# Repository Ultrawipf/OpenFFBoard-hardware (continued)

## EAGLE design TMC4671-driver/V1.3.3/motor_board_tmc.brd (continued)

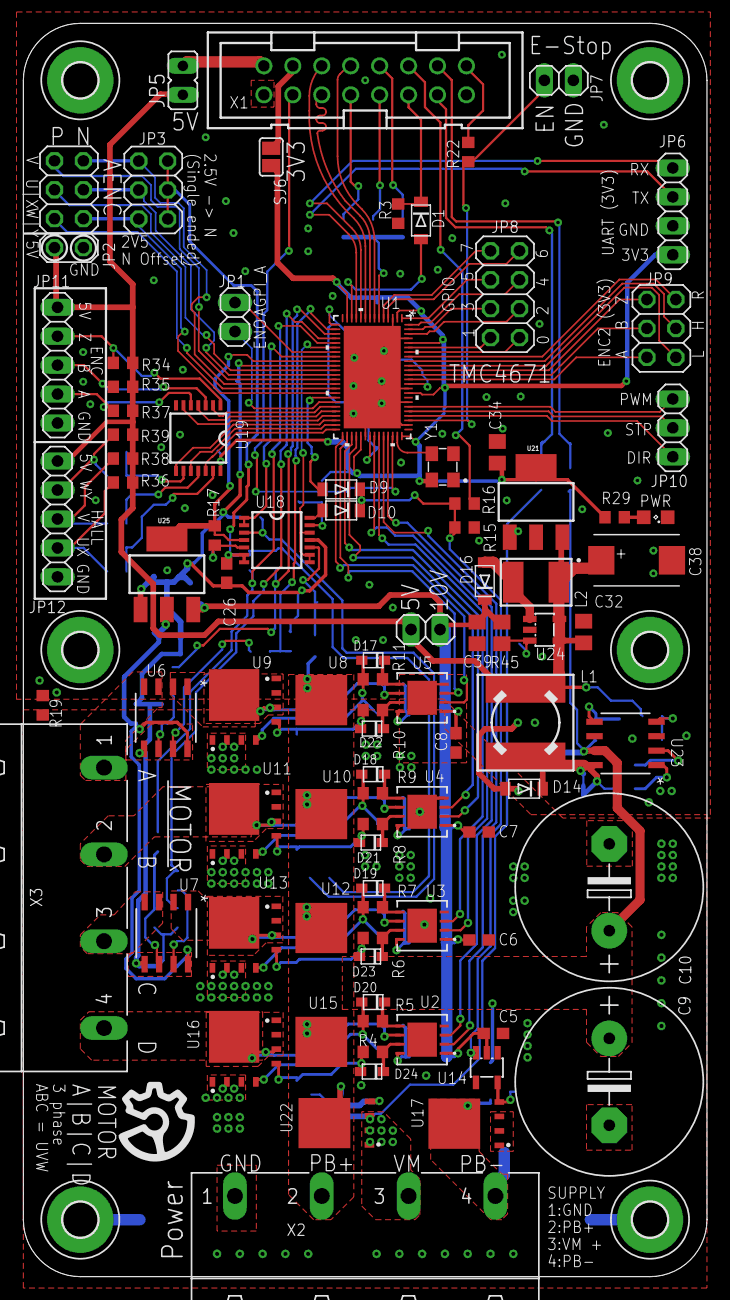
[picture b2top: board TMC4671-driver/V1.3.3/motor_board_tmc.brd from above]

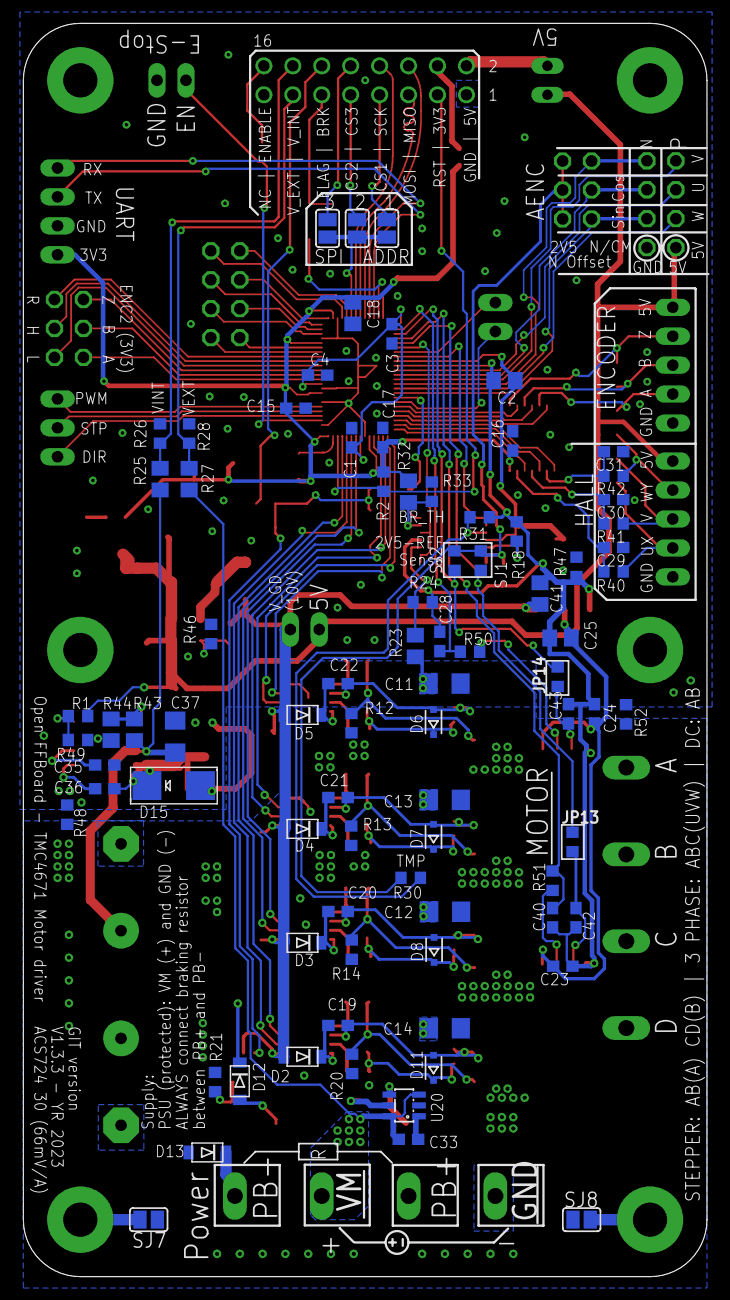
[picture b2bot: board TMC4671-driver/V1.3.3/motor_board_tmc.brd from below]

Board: 2 copper layers, 60.0 x 110.0 mm, 178 parts (82 on the bottom side), 136 nets.

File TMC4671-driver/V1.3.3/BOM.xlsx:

Comment | Designator | Footprint | Notes
3.3V Ldo 1117 | U21 | SOT223
1.5k | R16, R22, R24, R29, R31, R40, R41, R42 | R0603
100nF | C1, C3, C4, C5, C6, C7, C8, C15, C16, C17, C19, C20, C21, C22, C23, C24, C26, C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 | C0603
10k | R2, R3, R15, R17, R18, R26, R28, R46 | R0603
ERTJ1VR103J | R30 | R0603 | digikey https://www.digikey.de/en/products/detail/panasonic-electron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
10µH LQH43PN100M26L | L2 | L4532P | digikey
4.7nF | C42, C43,C29, C30, C31 | C0603 |  |  | Depends on sensor variant
1µF | C11, C12, C13, C14, C37 | C1206
15 | R4, R5, R6, R7, R8, R9, R10, R11 | R0603
220µH 74404084221 | L1 | 8MM INDUCTOR | digikey
25MHz | Y1 | ECS-327KE-TR
294k | R25, R27, R43 | R0805
33k | R12, R13, R14, R20, R21 | R0603
4.7k | R34, R35, R36, R37, R38, R39 | R0603
10µF | C2, C18, C25, C32, C34, C39, C41 | C0805
47k | R33 | R0603 |  |  | Brake resistor emergency point
593D476X0016D2TE3 | C38 | CAPPM7343X310N
680µF EEU-FS1K681B | C9, C10 | E7,5-16 | https://www.digikey.de/en/products/detail/panasonic-electron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 |  | https://www.arrow.com/en/products/eeu-fs1k681b/panasonic?q=E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
71.5k | R23, R32, R44, R45 | R0805
74LV17APWJ | U19 | TSSOP14 | digikey
AP3012KTR-G1 | U24 | SOT23-5L
NTMFSC2D9N08H | U8, U9, U10, U11, U12, U13, U15, U16, U17,U22 | POWERTFDN8 | Or FDMS86181, BSC030N08NS5 (20ohm gates minimum)
BZX384-XXX | D6, D7, D8, D11 | SOD323-R
Green | LED1 | SML0805
HV >100V | D2, D3, D4, D5, D12, D14 | SOD-123FL | Must handle 500mA+
LM5109BSD | U2, U3, U4, U5 | SDC08A
LM74700-Q1 | U20 | SOT23-6 | https://www.digikey.de/en/products/detail/texas-instruments/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
LV low drop diode (<10V) | D1, D9, D10, D16 | SOD-123FL | Fast gate discharge
max5035dasa | U23 | 8-SOIC
MCP1402T-E | U14 | SOT23-5L
MCP6004 | U18 | TSSOP14
TMC4671 | U1 | QFN76_10P5X6P5
5V LDO 1117 | U25 | SOT223
STPS30120DJF-TR | (U22) | PowerFLAT-5x6 | If no LM74700 is used. Otherwise use another mosfet here
SMA HV diode | D15 | SMA Diode | For DC converter
ACS724 | U6,U7
0 | R50,R51,R47, R48 | R0603 | For ACS724
0 | sj1,sj2,SJ3 | R0805 | For ACS724
47k | R1 | R0603 | 5v FB for max5035D
15k | R49 | R0603

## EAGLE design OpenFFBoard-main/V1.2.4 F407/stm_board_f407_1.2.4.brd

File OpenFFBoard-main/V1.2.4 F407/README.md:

### FFBoard main USB interface F407VG
This is the heart of the Open FFBoard.
It runs the FFBoard firmware and interfaces with all your peripherals and motor drivers.

V1.2.3 and 1.2.4 is a USB-C version and adds additional USB protections.
The SPI1 port layout had to change to 2 rows instead of 1.

#### How to order yourself
You can order this board directly via [jlcpcb.com](https://jlcpcb.com/?from=Gigawipf).

The BOM and component placement files are available in the JLC assembly folder and already formatted with matching LCSC part numbers.

Everything apart from the headers can be directly assembled by JLC including the USB socket.

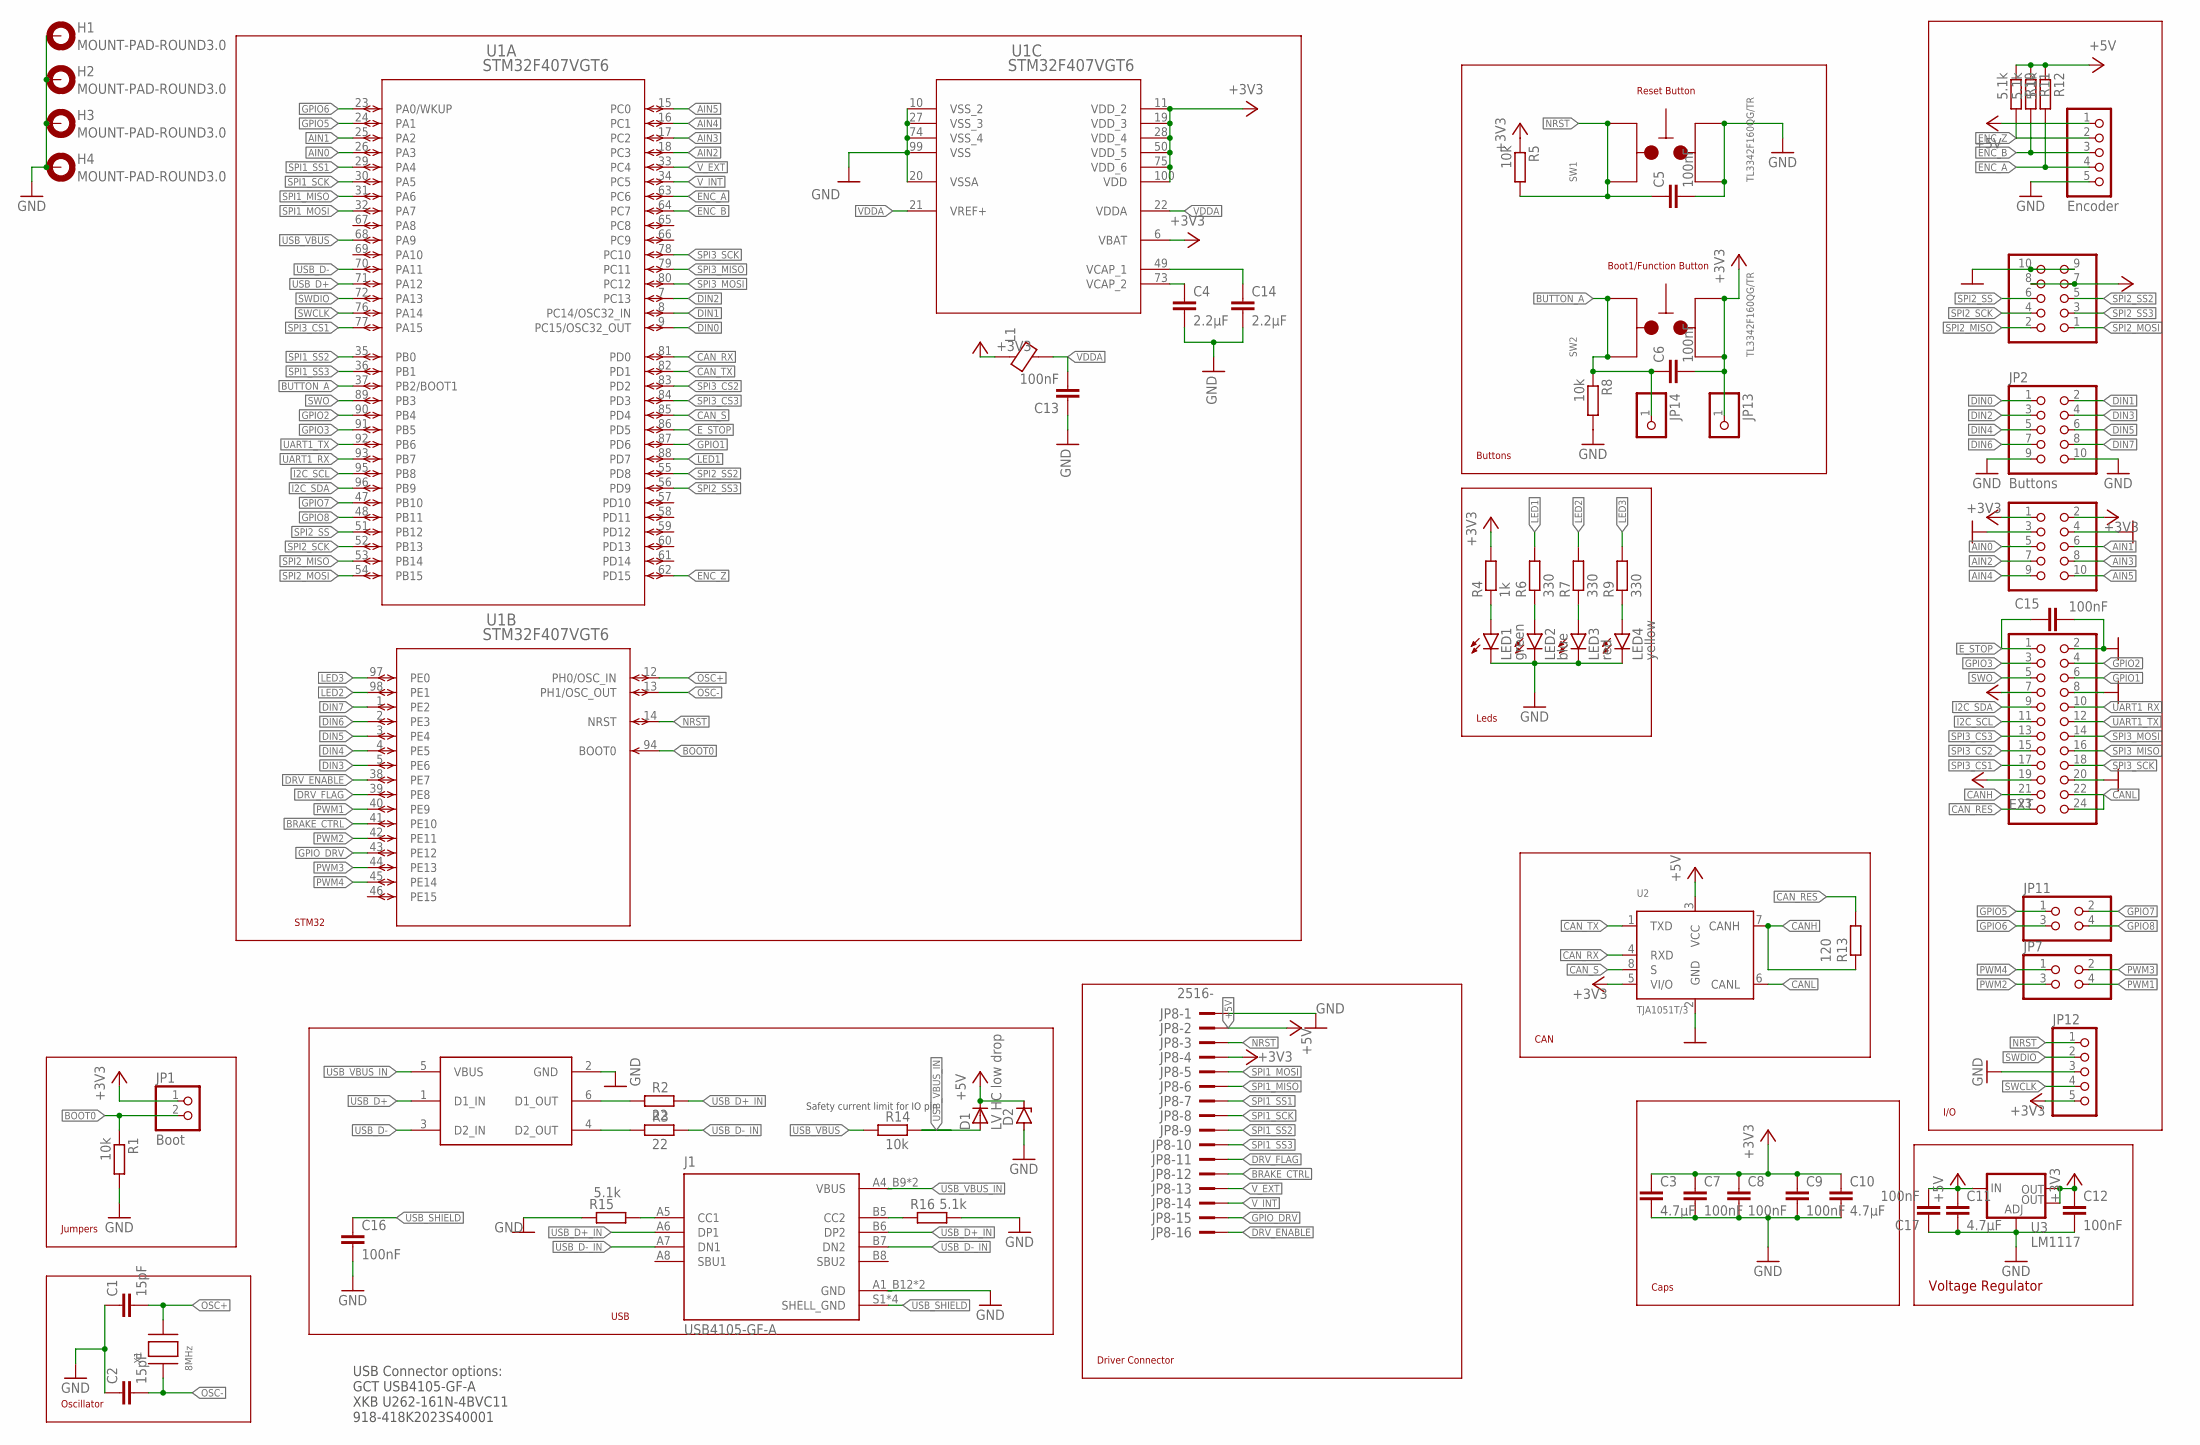
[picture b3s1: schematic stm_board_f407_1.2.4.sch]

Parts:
C1, C2: 15pF; C0603
C3, C10, C11: 4.7µF; C0805
C4, C14: 2.2µF; C0603
C5, C6, C7, C8, C9, C12, C13, C15, C16, C17: 100nF; C0603
D1: LV HC low drop; SMADIODE
D2: ZENER-DIODESOD80C; SOD80C
H1, H2, H3, H4: MOUNT-PAD-ROUND3.0; 3,0-PAD
J1: USB4105-GF-A; GCT_USB4105-GF-A
JP1: Boot; 1X02
JP2: Buttons; 2X05
JP3: Analog; 2X05
JP4: EXT; 2X12
JP5: Encoder; 1X05
JP6: SPI; 2X05
JP7, JP11: PINHD-2X2; 2X02
JP8: 2516-; PAK100/2500-16
JP12: PINHD-1X5; 1X05
JP13, JP14: PINHD-1X1; 1X01
L1: GZ2012D601TF; BLM21PG331SN1D
LED1: green; SML0805
LED2: blue; SML0805
LED3: red; SML0805
LED4: yellow; SML0805
R1, R5, R8, R14: 10k; R0603
R2, R3: 22; R0603
R4: 1k; R0603
R6, R7, R9: 330; R0603
R10, R11, R12, R15, R16: 5.1k; R0603
R13: 120; R0603
SW1, SW2: TL3342F160QG/TR
U1: STM32F407VGT6; LQFP100-14X14MM
U2: TJA1051T/3; SOT96-1
U3: LM1117; SOT223
U4: USBLC6-2SC6; TSOT-23-6
X1: 8MHz; NX5032

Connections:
+3V3: C3.1, C6.2, C7.1, C8.1, C9.1, C10.1, C12.1, JP1.1, JP3.1, JP3.2, JP4.7, JP6.7, JP6.8, JP8.4, JP12.5, JP13.1, L1.1, R4.2, R5.1, SW2.1, SW2.2, U1.6 (VBAT), U1.11 (VDD_2), U1.19 (VDD_3), U1.28 (VDD_4), U1.50 (VDD_5), U1.75 (VDD_6), U1.100 (VDD), U2.5 (VI/O), U3.2 (OUT), U3.4 (OUT)
+5V: C11.1, C17.2, D1.C, D2.C, JP4.19, JP5.1, JP8.2, R10.1, R11.1, R12.1, U2.3 (VCC), U3.3 (IN)
AIN0: JP3.5, U1.26 (PA3)
AIN1: JP3.6, U1.25 (PA2)
AIN2: JP3.7, U1.18 (PC3)
AIN3: JP3.8, U1.17 (PC2)
AIN4: JP3.9, U1.16 (PC1)
AIN5: JP3.10, U1.15 (PC0)
BOOT0: JP1.2, R1.1, U1.94 (BOOT0)
BRAKE_CTRL: JP8.12, U1.41 (PE10)
BUTTON_A: C6.1, JP14.1, R8.1, SW2.3, SW2.4, U1.37 (PB2/BOOT1)
CANH: JP4.21, R13.1, U2.7 (CANH)
CANL: JP4.22, JP4.24, U2.6 (CANL)
CAN_RES: JP4.23, R13.2
CAN_RX: U1.81 (PD0), U2.4 (RXD)
CAN_S: U1.85 (PD4), U2.8 (S)
CAN_TX: U1.82 (PD1), U2.1 (TXD)
DIN0: JP2.1, U1.9 (PC15/OSC32_OUT)
DIN1: JP2.2, U1.8 (PC14/OSC32_IN)
DIN2: JP2.3, U1.7 (PC13)
DIN3: JP2.4, U1.5 (PE6)
DIN4: JP2.5, U1.4 (PE5)
DIN5: JP2.6, U1.3 (PE4)
DIN6: JP2.7, U1.2 (PE3)
DIN7: JP2.8, U1.1 (PE2)
DRV_ENABLE: JP8.16, U1.38 (PE7)
DRV_FLAG: JP8.11, U1.39 (PE8)
ENC_A: JP5.4, R12.2, U1.63 (PC6)
ENC_B: JP5.3, R11.2, U1.64 (PC7)
ENC_Z: JP5.2, R10.2, U1.62 (PD15)
E_STOP: C15.1, JP4.1, U1.86 (PD5)
GND: C1.1, C2.1, C3.2, C4.2, C5.2, C7.2, C8.2, C9.2, C10.2, C11.2, C12.2, C13.1, C14.2, C15.2, C16.2, C17.1, D2.A, H1.B3,0, H2.B3,0, H3.B3,0, H4.B3,0, J1.A1_B12 (GND), J1.B1_A12 (GND), JP2.9, JP2.10, JP3.3, JP3.4, JP4.2, JP4.8, JP4.20, JP5.5, JP6.9, JP6.10, JP8.1, JP12.3, LED1.C, LED2.C, LED3.C, LED4.C, R1.2, R8.2, R15.1, R16.2, SW1.1, SW1.2, U1.10 (VSS_2), U1.20 (VSSA), U1.27 (VSS_3), U1.74 (VSS_4), U1.99 (VSS), U2.2 (GND), U3.1 (ADJ), U4.2 (GND)
GPIO1: JP4.6, U1.87 (PD6)
GPIO2: JP4.4, U1.90 (PB4)
GPIO3: JP4.3, U1.91 (PB5)
GPIO5: JP11.1, U1.24 (PA1)
GPIO6: JP11.3, U1.23 (PA0/WKUP)
GPIO7: JP11.2, U1.47 (PB10)
GPIO8: JP11.4, U1.48 (PB11)
GPIO_DRV: JP8.15, U1.43 (PE12)
I2C_SCL: JP4.11, U1.95 (PB8)
I2C_SDA: JP4.9, U1.96 (PB9)
LED1: R6.2, U1.88 (PD7)
LED2: R7.2, U1.98 (PE1)
LED3: R9.2, U1.97 (PE0)
unnamed: R2.1, U4.6 (D1_OUT)
unnamed: LED4.A, R9.1
unnamed: C14.1, U1.49 (VCAP_1)
unnamed: J1.B5 (CC2), R16.1
unnamed: J1.A5 (CC1), R15.2
unnamed: C4.1, U1.73 (VCAP_2)
unnamed: R3.1, U4.4 (D2_OUT)
unnamed: LED1.A, R4.1
unnamed: LED2.A, R6.1
unnamed: LED3.A, R7.1
NRST: C5.1, JP8.3, JP12.1, R5.2, SW1.3, SW1.4, U1.14 (NRST)
OSC+: C1.2, U1.12 (PH0/OSC_IN), X1.P$2
OSC-: C2.2, U1.13 (PH1/OSC_OUT), X1.P$1
PWM1: JP7.4, U1.40 (PE9)
PWM2: JP7.3, U1.42 (PE11)
PWM3: JP7.2, U1.44 (PE13)
PWM4: JP7.1, U1.45 (PE14)
SPI1_MISO: JP8.6, U1.31 (PA6)
SPI1_MOSI: JP8.5, U1.32 (PA7)
SPI1_SCK: JP8.8, U1.30 (PA5)
SPI1_SS1: JP8.7, U1.29 (PA4)
SPI1_SS2: JP8.9, U1.35 (PB0)
SPI1_SS3: JP8.10, U1.36 (PB1)
SPI2_MISO: JP6.2, U1.53 (PB14)
SPI2_MOSI: JP6.1, U1.54 (PB15)
SPI2_SCK: JP6.4, U1.52 (PB13)
SPI2_SS: JP6.6, U1.51 (PB12)
SPI2_SS2: JP6.5, U1.55 (PD8)
SPI2_SS3: JP6.3, U1.56 (PD9)
SPI3_CS1: JP4.17, U1.77 (PA15)
SPI3_CS2: JP4.15, U1.83 (PD2)
SPI3_CS3: JP4.13, U1.84 (PD3)
SPI3_MISO: JP4.16, U1.79 (PC11)
SPI3_MOSI: JP4.14, U1.80 (PC12)
SPI3_SCK: JP4.18, U1.78 (PC10)
SWCLK: JP12.4, U1.76 (PA14)
SWDIO: JP12.2, U1.72 (PA13)
SWO: JP4.5, U1.89 (PB3)
UART1_RX: JP4.10, U1.93 (PB7)
UART1_TX: JP4.12, U1.92 (PB6)
USB_D+: U1.71 (PA12), U4.1 (D1_IN)
USB_D+_IN: J1.A6 (DP1), J1.B6 (DP2), R2.2
USB_D-: U1.70 (PA11), U4.3 (D2_IN)
USB_D-_IN: J1.A7 (DN1), J1.B7 (DN2), R3.2
USB_SHIELD: C16.1, J1.S1 (SHELL_GND), J1.S2 (SHELL_GND), J1.S3 (SHELL_GND), J1.S4 (SHELL_GND)
USB_VBUS: R14.1, U1.68 (PA9)
USB_VBUS_IN: D1.A, J1.A4_B9 (VBUS), J1.B4_A9 (VBUS), R14.2, U4.5 (VBUS)
VDDA: C13.2, L1.2, U1.21 (VREF+), U1.22 (VDDA)
V_EXT: JP8.13, U1.33 (PC4)
V_INT: JP8.14, U1.34 (PC5)

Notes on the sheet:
Oscillator
USB
Boot1/Function Button
Reset Button
Buttons
Jumpers
Leds
Voltage Regulator
I/O
Driver Connector
Caps
STM32
Safety current limit for IO pin
CAN
USB Connector options: GCT USB4105-GF-A XKB U262-161N-4BVC11 918-418K2023S40001

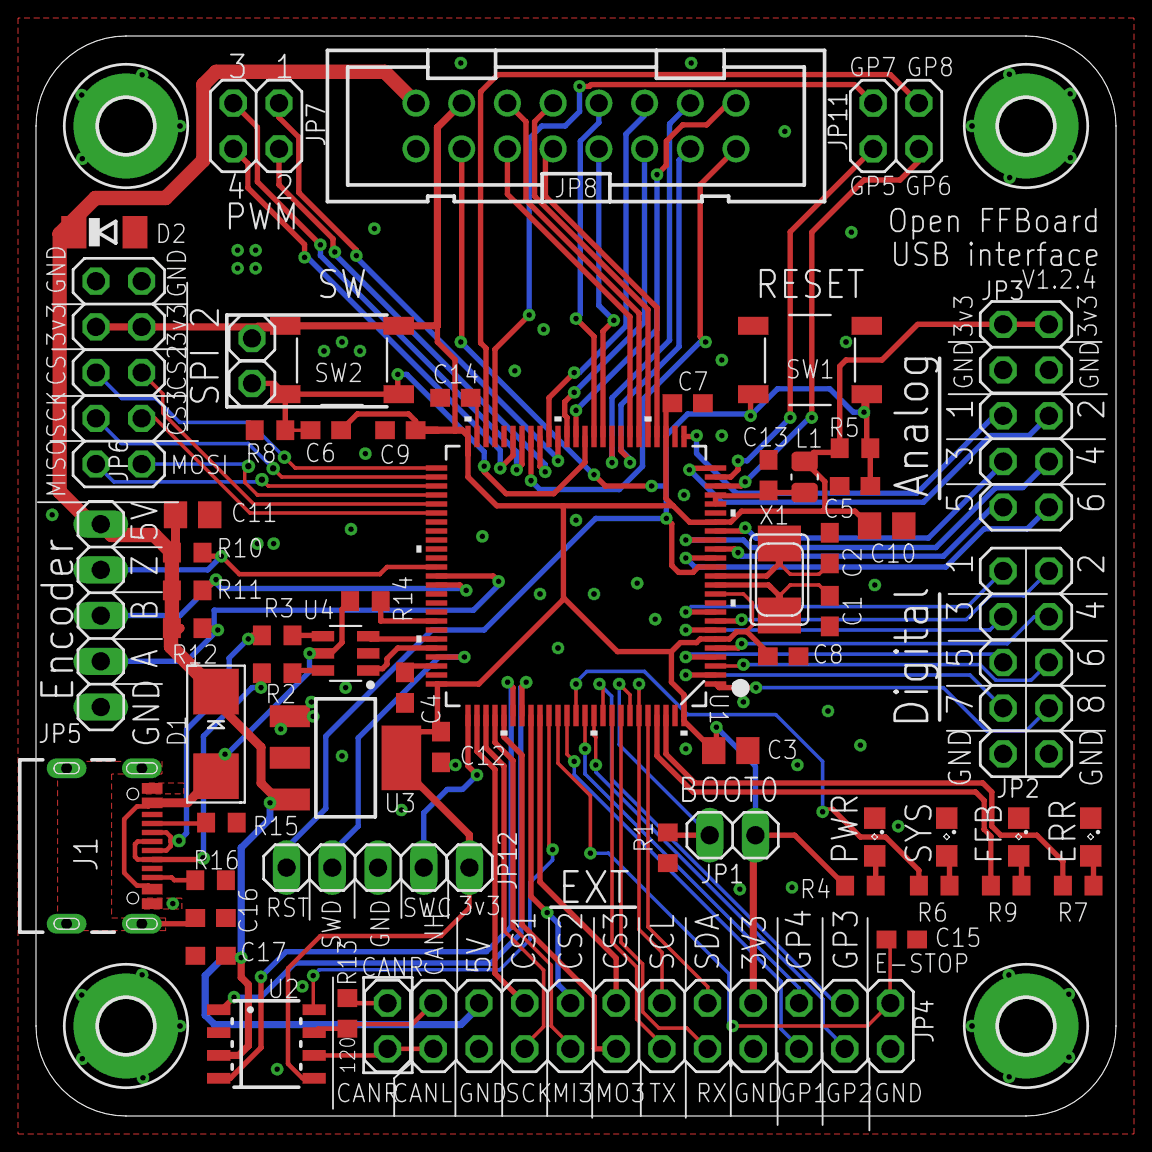
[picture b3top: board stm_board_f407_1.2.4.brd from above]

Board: 2 copper layers, 60.0 x 60.0 mm, 64 parts (0 on the bottom side), 95 nets.

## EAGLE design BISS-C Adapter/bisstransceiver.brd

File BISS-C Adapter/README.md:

## BISS-C module

This module allows the OpenFFBoard to use its SPI3 (EXT) header to communicate with common BISS-C encoders like the JKD-4-22PF-G05BL (used on Mige motors).

The SUB-D 15 female connector matches the pinout of Mige motors and some others directly.

The CS pin connection is optional. When left disconnected or low the transceivers are active, when high the transceivers are off.

The BISS-C encoder module can only be used with certain motor driver modes:

-   TMC via forwarding

-   VESC as secondary encoder

-   PWM

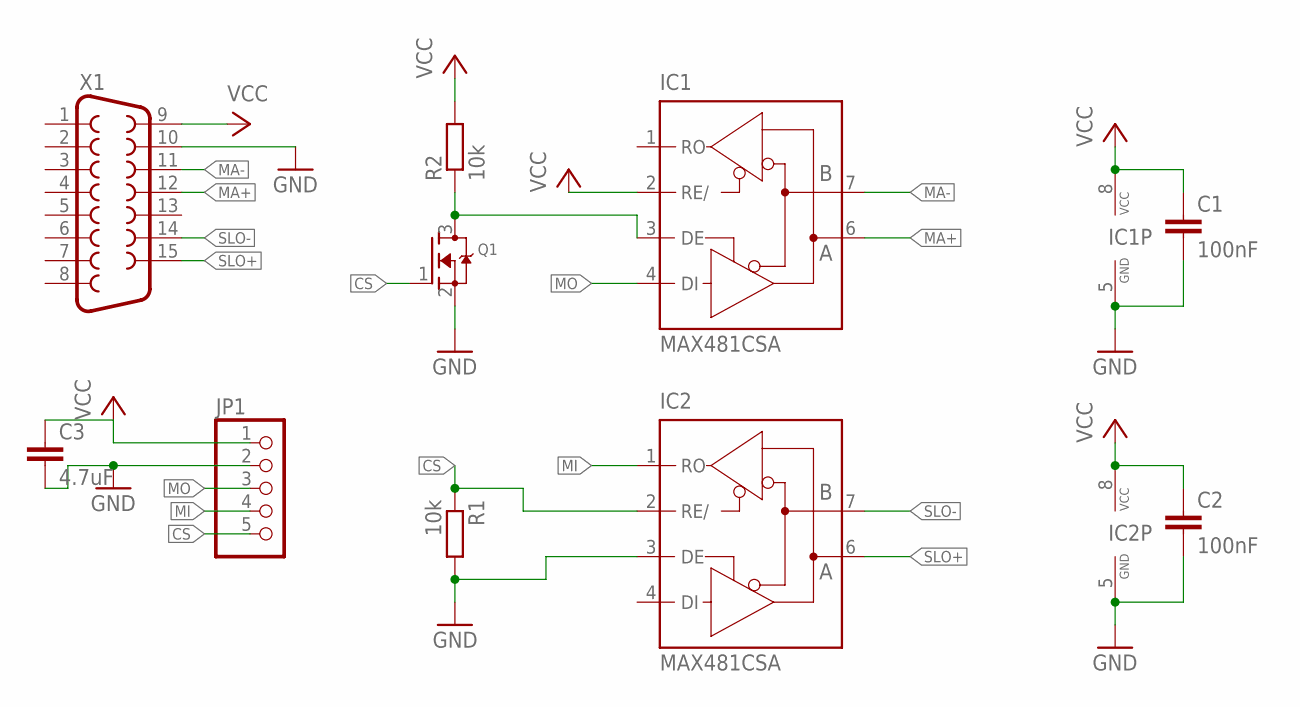
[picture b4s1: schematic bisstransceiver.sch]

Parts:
C1, C2: 100nF; C0603
C3: 4.7uF; C0603
IC1, IC2: MAX481CSA; SO08
JP1: PINHD-1X5/90; 1X05/90
Q1: MOSFET-NREFLOW; SOT23
R1, R2: 10k; R0603
X1: F15HP

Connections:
CS: IC2.2 (RE/), JP1.5, Q1.1 (G), R1.1
GND: C1.2, C2.2, C3.2, IC1.5 (GND), IC2.3 (DE), IC2.5 (GND), JP1.2, Q1.2 (S), R1.2, X1.10
MA+: IC1.6 (A), X1.12
MA-: IC1.7 (B), X1.11
MI: IC2.1 (RO), JP1.4
MO: IC1.4 (DI), JP1.3
unnamed: IC1.3 (DE), Q1.3 (D), R2.1
SLO+: IC2.6 (A), X1.15
SLO-: IC2.7 (B), X1.14
VCC: C1.1, C2.1, C3.1, IC1.2 (RE/), IC1.8 (VCC), IC2.8 (VCC), JP1.1, R2.2, X1.9

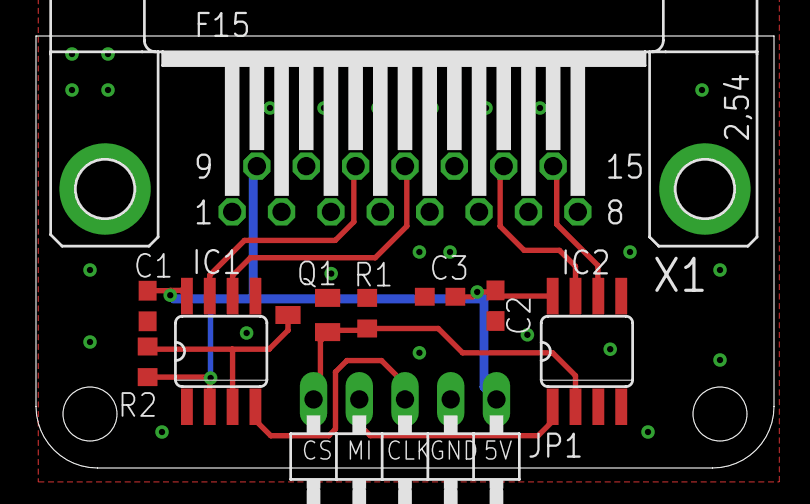
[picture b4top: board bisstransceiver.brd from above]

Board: 2 copper layers, 41.0 x 24.0 mm, 10 parts (0 on the bottom side), 10 nets.

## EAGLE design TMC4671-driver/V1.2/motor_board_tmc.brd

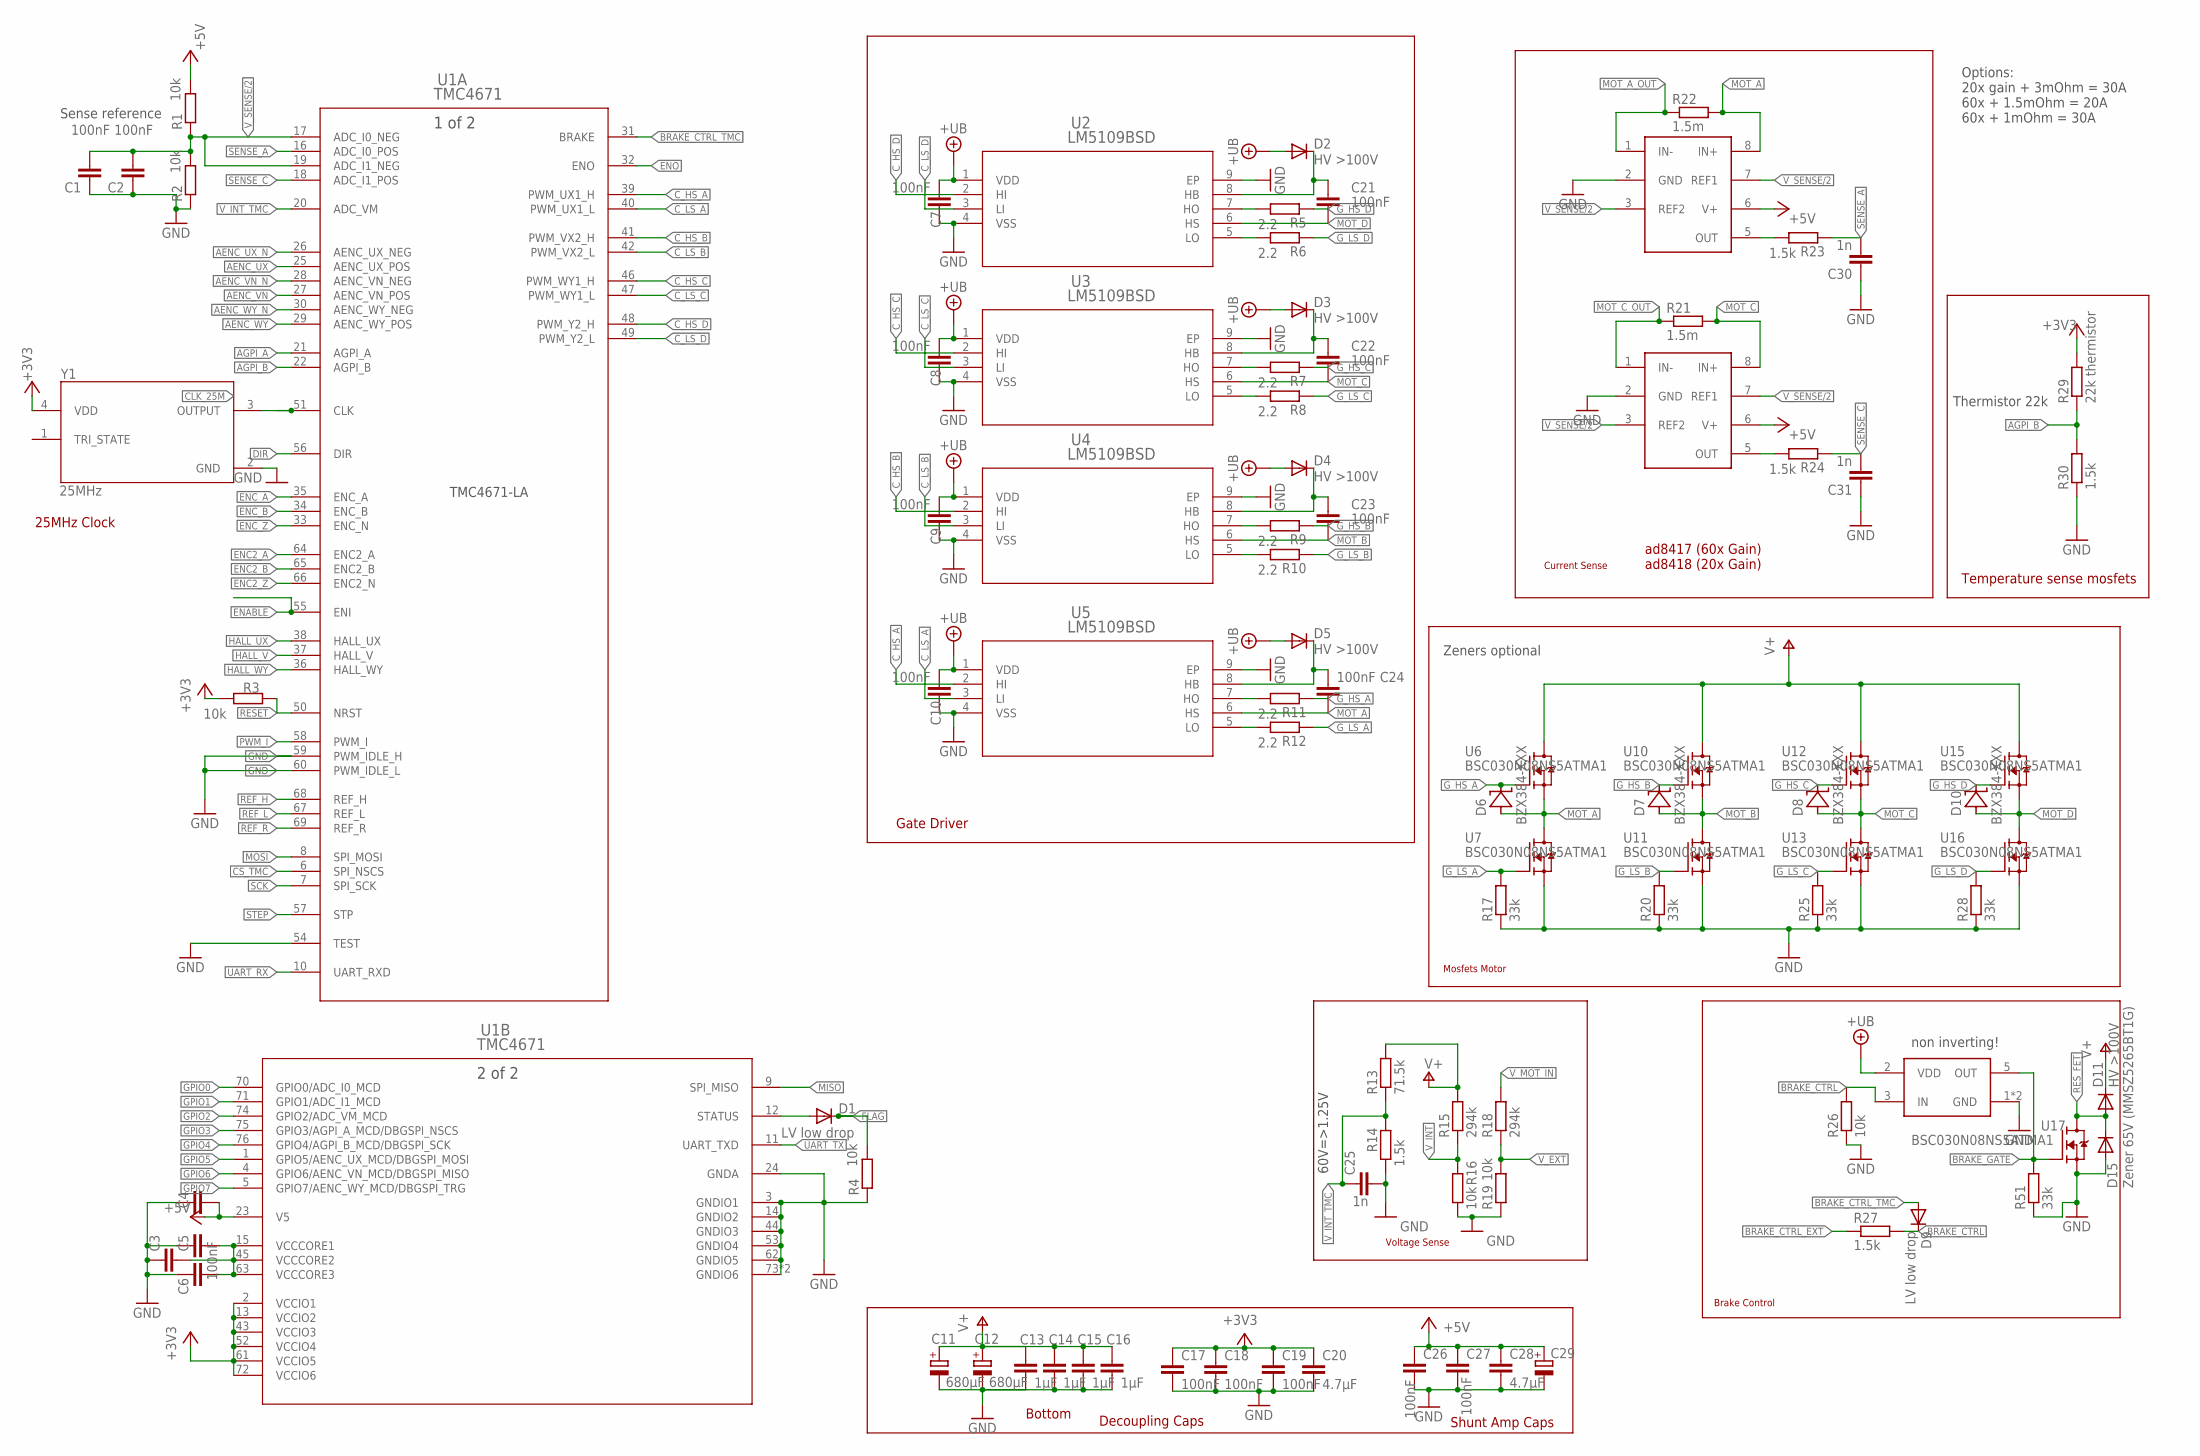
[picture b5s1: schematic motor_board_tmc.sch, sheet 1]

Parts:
C1, C2, C3, C4, C5, C6, C7, C8, C9, C10, C17, C18, C19, C26, C27: 100nF; C0603
C11, C12: 680µF; E7,5-16
C13, C14, C15, C16: 1µF; C1206
C20, C28: 4.7µF; C0805
C21, C22, C23, C24: 100nF; C0805
C25, C30, C31: 1n; C0603
C29: CPOL-EUE5-8.5; E5-8,5
D1, D9: LV low drop; SOD-123FL
D2, D3, D4, D5, D11: HV >100V; SOD-123FL
D6, D7, D8, D10: BZX384-XXX; SOD323-R
D15: Zener 65V (MMSZ5265BT1G); SOD-123FL
R1, R2, R3, R4, R16, R19, R26: 10k; R0603
R5, R6, R7, R8, R9, R10, R11, R12: 2.2; R0603
R13: 71.5k; R0805
R14, R23, R24, R27, R30: 1.5k; R0603
R15, R18: 294k; R0805
R17, R20, R25, R28, R51: 33k; R0603
R21, R22: 1.5m; R2512
R29: 22k thermistor; R0603
U1: TMC4671; QFN76_10P5X6P5
U2, U3, U4, U5: LM5109BSD; SDC08A
U6, U7, U10, U11, U12, U13, U15, U16, U17: BSC030N08NS5ATMA1; MOSFET_BSC093N04LSGATMA1
U8, U9: AD841X; MSOP8
U14: MCP14XX; SOT23-5L
Y1: 25MHz; ECS-327KE-TR

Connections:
+3V3: C17.1, C18.1, C19.1, C20.1, R3.2, R29.2, U1.2 (VCCIO1), U1.13 (VCCIO2), U1.43 (VCCIO3), U1.52 (VCCIO4), U1.61 (VCCIO5), U1.72 (VCCIO6), Y1.4 (VDD); also elsewhere on the board
+5V: C4.2, C26.1, C27.1, C28.1, C29.+, R1.2, U1.23 (V5), U8.6 (V+), U9.6 (V+); also elsewhere on the board
AENC_UX: U1.25 (AENC_UX_POS); also elsewhere on the board
AENC_UX_N: U1.26 (AENC_UX_NEG); also elsewhere on the board
AENC_VN: U1.27 (AENC_VN_POS); also elsewhere on the board
AENC_VN_N: U1.28 (AENC_VN_NEG); also elsewhere on the board
AENC_WY: U1.29 (AENC_WY_POS); also elsewhere on the board
AENC_WY_N: U1.30 (AENC_WY_NEG); also elsewhere on the board
AGPI_A: U1.21 (AGPI_A); also elsewhere on the board
AGPI_B: R29.1, R30.2, U1.22 (AGPI_B)
BRAKE_CTRL: D9.C, R26.2, R27.2, U14.3 (IN)
BRAKE_CTRL_EXT: R27.1; also elsewhere on the board
BRAKE_CTRL_TMC: D9.A, U1.31 (BRAKE)
BRAKE_GATE: R51.2, U14.5 (OUT), U17.4 (G)
CLK_25M: U1.51 (CLK), Y1.3 (OUTPUT)
CS_TMC: U1.6 (SPI_NSCS); also elsewhere on the board
C_HS_A: U1.39 (PWM_UX1_H), U5.2 (HI)
C_HS_B: U1.41 (PWM_VX2_H), U4.2 (HI)
C_HS_C: U1.46 (PWM_WY1_H), U3.2 (HI)
C_HS_D: U1.48 (PWM_Y2_H), U2.2 (HI)
C_LS_A: U1.40 (PWM_UX1_L), U5.3 (LI)
C_LS_B: U1.42 (PWM_VX2_L), U4.3 (LI)
C_LS_C: U1.47 (PWM_WY1_L), U3.3 (LI)
C_LS_D: U1.49 (PWM_Y2_L), U2.3 (LI)
DIR: U1.56 (DIR); also elsewhere on the board
ENABLE: U1.55 (ENI); also elsewhere on the board
ENC2_A: U1.64 (ENC2_A); also elsewhere on the board
ENC2_B: U1.65 (ENC2_B); also elsewhere on the board
ENC2_Z: U1.66 (ENC2_N); also elsewhere on the board
ENC_A: U1.35 (ENC_A); also elsewhere on the board
ENC_B: U1.34 (ENC_B); also elsewhere on the board
ENC_Z: U1.33 (ENC_N); also elsewhere on the board
ENO: U1.32 (ENO); also elsewhere on the board
FLAG: D1.C, R4.2; also elsewhere on the board
GND: C1.1, C2.1, C3.1, C4.1, C5.1, C6.1, C7.1, C8.1, C9.1, C10.1, C11.-, C12.-, C13.2, C14.2, C15.2, C16.2, C17.2, C18.2, C19.2, C20.2, C25.2, C26.2, C27.2, C28.2, C29.-, C30.1, C31.1, D15.A, R2.1, R4.1, R14.1, R16.1, R17.1, R19.1, R20.1, R25.1, R26.1, R28.1, R30.1, R51.1, U1.3 (GNDIO1), U1.14 (GNDIO2), U1.24 (GNDA), U1.44 (GNDIO3), U1.53 (GNDIO4), U1.54 (TEST), U1.59 (PWM_IDLE_H), U1.60 (PWM_IDLE_L), U1.62 (GNDIO5), U1.73 (GNDIO6), U1.77 (GNDIO6), U2.4 (VSS), U2.9 (EP), U3.4 (VSS), U3.9 (EP), U4.4 (VSS), U4.9 (EP), U5.4 (VSS), U5.9 (EP), U7.1 (S), U7.2 (S), U7.3 (S), U8.2 (GND), U9.2 (GND), U11.1 (S), U11.2 (S), U11.3 (S), U13.1 (S), U13.2 (S), U13.3 (S), U14.1 (GND), U14.4 (GND), U16.1 (S), U16.2 (S), U16.3 (S), U17.1 (S), U17.2 (S), U17.3 (S), Y1.2 (GND); also elsewhere on the board
GPIO0: U1.70 (GPIO0/ADC_I0_MCD); also elsewhere on the board
GPIO1: U1.71 (GPIO1/ADC_I1_MCD); also elsewhere on the board
GPIO2: U1.74 (GPIO2/ADC_VM_MCD); also elsewhere on the board
GPIO3: U1.75 (GPIO3/AGPI_A_MCD/DBGSPI_NSCS); also elsewhere on the board
GPIO4: U1.76 (GPIO4/AGPI_B_MCD/DBGSPI_SCK); also elsewhere on the board
GPIO5: U1.1 (GPIO5/AENC_UX_MCD/DBGSPI_MOSI); also elsewhere on the board
GPIO6: U1.4 (GPIO6/AENC_VN_MCD/DBGSPI_MISO); also elsewhere on the board
GPIO7: U1.5 (GPIO7/AENC_WY_MCD/DBGSPI_TRG); also elsewhere on the board
G_HS_A: D6.C, R11.1, U6.4 (G)
G_HS_B: D7.C, R9.1, U10.4 (G)
G_HS_C: D8.C, R7.1, U12.4 (G)
G_HS_D: D10.C, R5.1, U15.4 (G)
G_LS_A: R12.1, R17.2, U7.4 (G)
G_LS_B: R10.1, R20.2, U11.4 (G)
G_LS_C: R8.1, R25.2, U13.4 (G)
G_LS_D: R6.1, R28.2, U16.4 (G)
HALL_UX: U1.38 (HALL_UX); also elsewhere on the board
HALL_V: U1.37 (HALL_V); also elsewhere on the board
HALL_WY: U1.36 (HALL_WY); also elsewhere on the board
MISO: U1.9 (SPI_MISO); also elsewhere on the board
MOSI: U1.8 (SPI_MOSI); also elsewhere on the board
MOT_A: C24.2, D6.A, R22.2, U5.6 (HS), U6.1 (S), U6.2 (S), U6.3 (S), U7.5 (D), U8.8 (IN+)
MOT_A_OUT: R22.1, U8.1 (IN-); also elsewhere on the board
MOT_B: C23.2, D7.A, U4.6 (HS), U10.1 (S), U10.2 (S), U10.3 (S), U11.5 (D); also elsewhere on the board
MOT_C: C22.2, D8.A, R21.2, U3.6 (HS), U9.8 (IN+), U12.1 (S), U12.2 (S), U12.3 (S), U13.5 (D)
MOT_C_OUT: R21.1, U9.1 (IN-); also elsewhere on the board
MOT_D: C21.2, D10.A, U2.6 (HS), U15.1 (S), U15.2 (S), U15.3 (S), U16.5 (D); also elsewhere on the board
unnamed: D1.A, U1.12 (STATUS)
unnamed: R23.2, U8.5 (OUT)
unnamed: R24.2, U9.5 (OUT)
unnamed: R12.2, U5.5 (LO)
unnamed: C24.1, D5.C, U5.8 (HB)
unnamed: R11.2, U5.7 (HO)
unnamed: C23.1, D4.C, U4.8 (HB)
unnamed: R10.2, U4.5 (LO)
unnamed: R9.2, U4.7 (HO)
unnamed: C21.1, D2.C, U2.8 (HB)
unnamed: R6.2, U2.5 (LO)
unnamed: R5.2, U2.7 (HO)
unnamed: C22.1, D3.C, U3.8 (HB)
unnamed: R8.2, U3.5 (LO)
unnamed: R7.2, U3.7 (HO)
PWM_I: U1.58 (PWM_I); also elsewhere on the board
REF_H: U1.68 (REF_H); also elsewhere on the board
REF_L: U1.67 (REF_L); also elsewhere on the board
REF_R: U1.69 (REF_R); also elsewhere on the board
RESET: R3.1, U1.50 (NRST); also elsewhere on the board
RES_FET: D11.A, D15.C, U17.5 (D); also elsewhere on the board
SCK: U1.7 (SPI_SCK); also elsewhere on the board
SENSE_A: C30.2, R23.1, U1.16 (ADC_I0_POS)
SENSE_C: C31.2, R24.1, U1.18 (ADC_I1_POS)
STEP: U1.57 (STP); also elsewhere on the board
UART_RX: U1.10 (UART_RXD); also elsewhere on the board
UART_TX: U1.11 (UART_TXD); also elsewhere on the board
V+: C11.+, C12.+, C13.1, C14.1, C15.1, C16.1, D11.C, R13.2, R15.2, U6.5 (D), U10.5 (D), U12.5 (D), U15.5 (D); also elsewhere on the board
VCORE: C3.2, C5.2, C6.2, U1.15 (VCCCORE1), U1.45 (VCCCORE2), U1.63 (VCCCORE3)
V_EXT: R18.1, R19.2; also elsewhere on the board
V_GD: C7.2, C8.2, C9.2, C10.2, D2.A, D3.A, D4.A, D5.A, U2.1 (VDD), U3.1 (VDD), U4.1 (VDD), U5.1 (VDD), U14.2 (VDD); also elsewhere on the board
V_INT: R15.1, R16.2; also elsewhere on the board
V_INT_TMC: C25.1, R13.1, R14.2, U1.20 (ADC_VM)
V_MOT_IN: R18.2; also elsewhere on the board
V_SENSE/2: C1.2, C2.2, R1.1, R2.2, U1.17 (ADC_I0_NEG), U1.19 (ADC_I1_NEG), U8.3 (REF2), U8.7 (REF1), U9.3 (REF2), U9.7 (REF1)

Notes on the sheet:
Mosfets Motor
Gate Driver
Current Sense
Voltage Sense
Brake Control
ad8417 (60x Gain) ad8418 (20x Gain)
Shunt Amp Caps
Decoupling Caps
25MHz Clock
Bottom
Sense reference
60V=>1.25V
Options: 20x gain + 3mOhm = 30A 60x + 1.5mOhm = 20A 60x + 1mOhm = 30A
Temperature sense mosfets
Thermistor 22k
Zeners optional
TMC4671-LA
non inverting!
